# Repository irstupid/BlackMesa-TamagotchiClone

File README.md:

# Tamagotchi Clone

my project for week... 4? of hackclub halflife.

the theme this week was display, and I rather like working with displays, so obviously my first thought was "how can I fix that?" I decided that the situation in which displays are the most annoying is battery critical electronics, and also small displays are a pain in the ass, so why not make it tiny? then I remembered this tamagotchi bag that I got after being scammed out of an actual tamagotchi by a gatcha machine and that's how this project was born.

# Components

for the display I use a crystalfontz CFAG12864T3-NFH, which is a LCD that has transflective coating behind it instead of a backlight making it super duper power efficient and also giving it the cool retro aesthetic of the display from the original tamagotchi and gameboy, but you cant see it in the dark

for the microcontroller I use a msp430g2553in20 because it is super power effecient and has the most RAM of any msp430 in a DIP package, which makes it easy to swap between the dev board (the MSP-EXP430G2ET) and the actual board

the battery is just a CR2450 coin cell

and the rotary encoder is just some adafruit something I had laying around.

# PCB

the main difficulty with this PCB was getting the shape right, I had to make the outline first in an onshape sketch and then record the positions of each circle and use those as the offsets for arcs in kicad, and then do some snapping shenanigans. kicad really wasn't meant for that kind of thing. after that it was pretty much just connect the dots. Also fitting in the battery was pretty gnarly. I am yet to do the flower pattern on the silkscreen and copper mask, I will tell you how that goes when I finish it!

also there are no manufacturing files yet because I'm gonna make those when I finish the board and this week dident require them

# Firmware

I haven't done the firmware yet because I don't have a microcontroller to test on.

I'm sure it will be very interesting though! I get to deal with a microcontroller I'm new to at a low level with the added difficulty of giving it narcolepsy and having the working memory of a goldfish.

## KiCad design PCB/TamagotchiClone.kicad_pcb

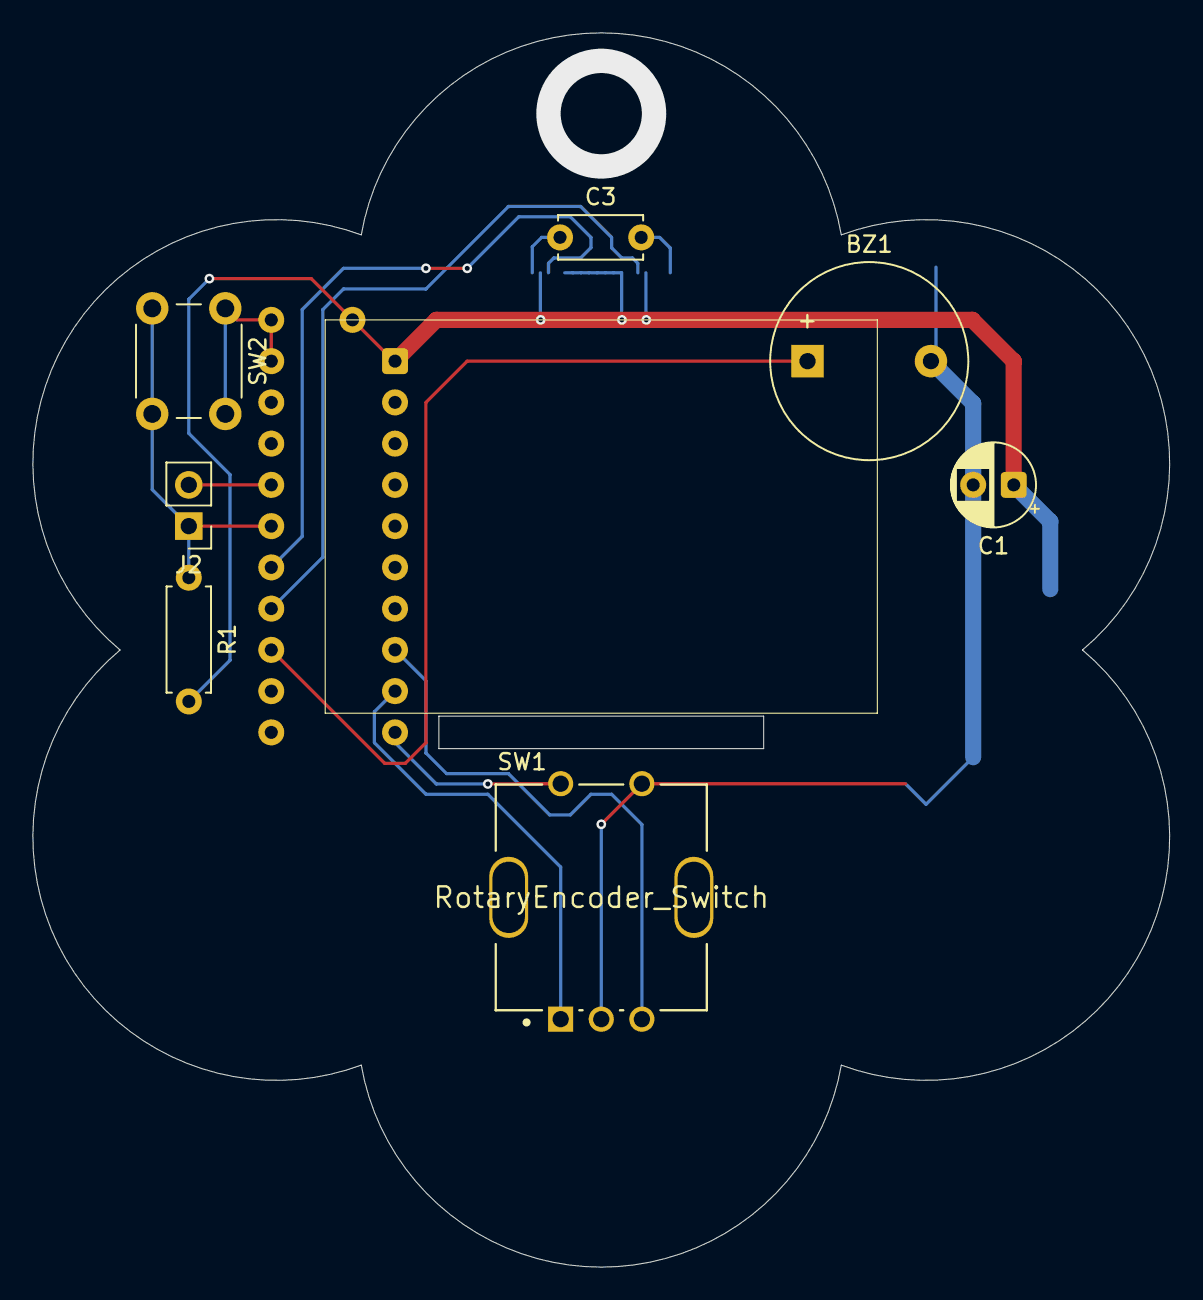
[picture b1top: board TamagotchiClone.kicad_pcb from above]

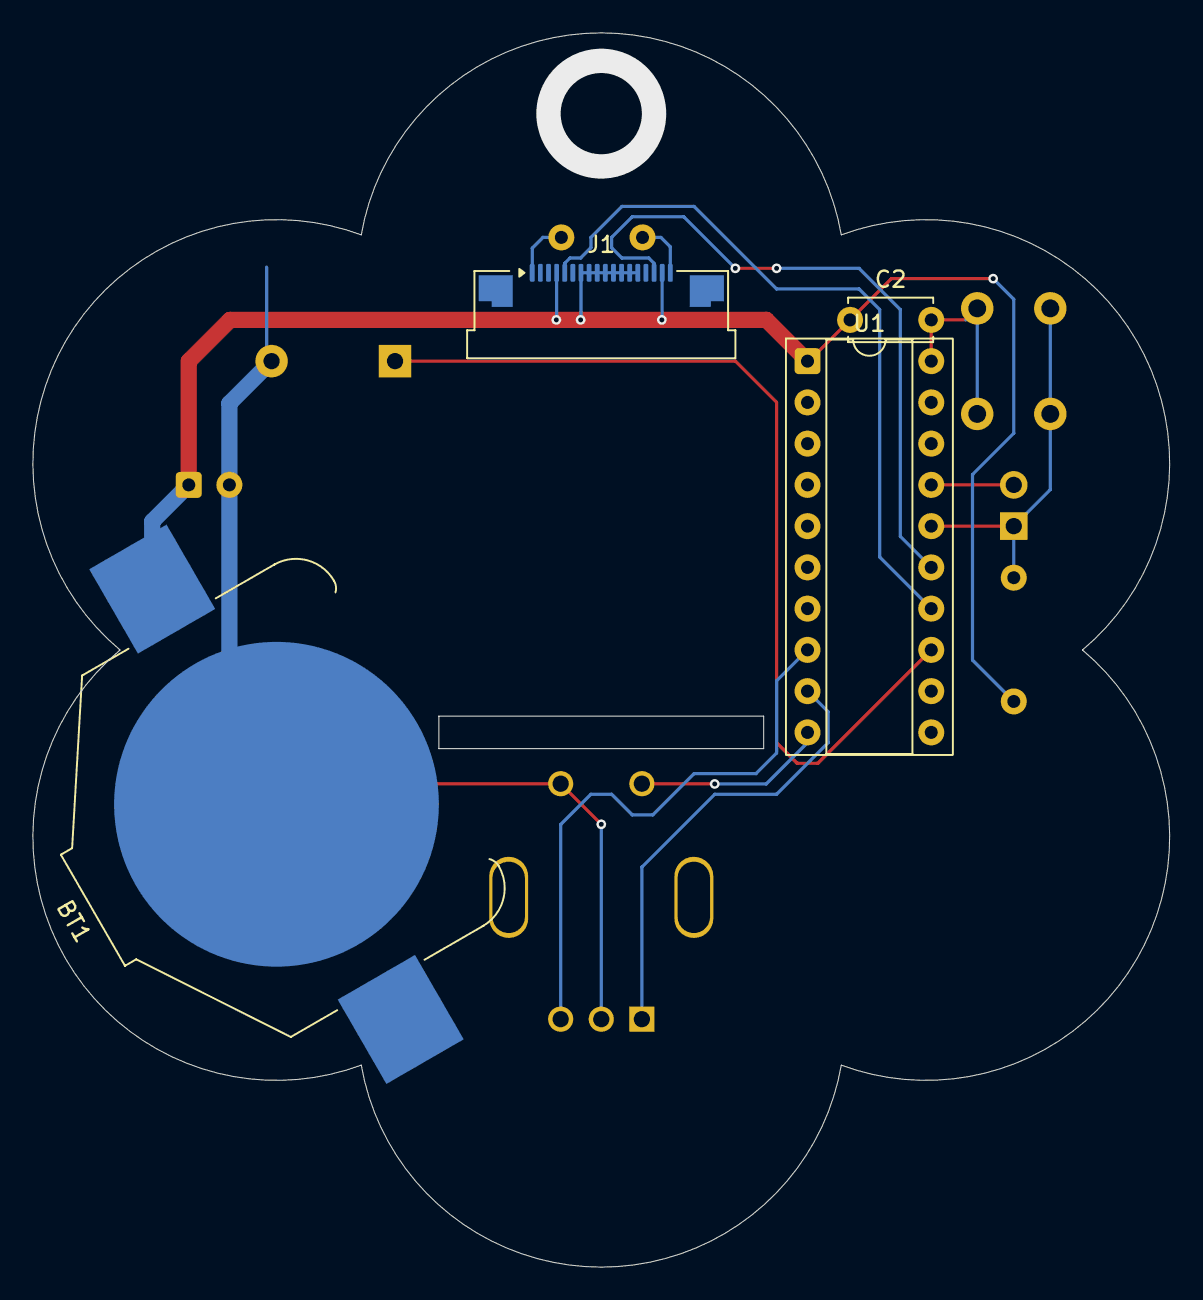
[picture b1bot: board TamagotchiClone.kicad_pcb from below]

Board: 2 copper layers, 70.0 x 76.0 mm, 11 parts (4 on the bottom side), 14 nets.

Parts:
BT1: Battery_Cell; BatteryHolder_Keystone_3008_1x2450
BZ1: Buzzer; Buzzer_12x9.5RM7.6
C1: C; CP_Radial_D5.0mm_P2.50mm
C2, C3: C; C_Disc_D5.0mm_W2.5mm_P5.00mm
J1: Conn_01x18_MountingPin; Amphenol_F32Q-1A7x1-11018_1x18-1MP_P0.5mm_Horizontal
J2: Conn_01x02_Pin; PinHeader_1x02_P2.54mm_Vertical
R1: R; R_Axial_DIN0207_L6.3mm_D2.5mm_P7.62mm_Horizontal
SW1: RotaryEncoder_Switch; Bourns-PEC11R-4220F-S0024-0-0-0
SW2: SW_Push; SW_PUSH_6mm
U1: MSP430G2553IN20; DIP-20_W7.62mm_Socket

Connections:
A: J1.6, U1.5 (CAOUT/VREF-/VeREF-/CA3/A3/P1.3)
BUZ: BZ1.1 (+), U1.13 (P2.5/TA1.2)
CS: J1.3, U1.6 (TCK/SMCLK/UCB0STE/UCA0CLK/VREF+/VeREF+/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)
DRST: J1.5, U1.14 (TDI/TCLK/UCB0SOMI/UCB0SCL/TA0.1/CA6/A6/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)
DVV: C3.2, J1.1, U1.4 (UCA0TXD/UCA0SIMO/TA0.1/CA2/A2/P1.2)
Gnd: BT1.2 (-), BZ1.2 (-), C1.2, C2.2, C3.1, J1.2, J1.18, SW1.C, SW1.S2, SW2.1, U1.20 (DVSS)
RA: SW1.A, U1.9 (P2.1/TA1.1)
RB: SW1.B, U1.8 (P2.0/TA1.0)
RST: J2.1, R1.1, SW2.2, U1.16 (~RST/NMI/SBWTDIO)
SPICLK: J1.15, U1.7 (TMS/UCB0CLK/UCA0STE/TA0.0/CA5/A5/P1.5)
SPIDI: J1.16, U1.15 (TDO/TDI/UCB0SIMO/UCB0SDA/CAOUT/CA7/A7/P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)
SW: SW1.S1, U1.10 (P2.2/TA1.1)
TEST: J2.2, U1.17 (TEST/SBWTCK)
Vcc: BT1.1 (+), C1.1, C2.1, J1.4, J1.7, J1.8, J1.9, J1.10, J1.11, J1.12, J1.13, J1.14, J1.17, R1.2, U1.1 (DVCC)
